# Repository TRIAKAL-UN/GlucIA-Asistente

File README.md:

# Proyecto GlucIA

## Home

### **Integrantes**
- Jeremy S. Arias Alegria
- David S. Ayala Salamanca
- Steven Cortes Gil
- Sara Duarte Acevedo
- David A. Orozco Gomez
- Oliver Emanuel Sucre Aular

---

### **Introducción**
GlucIA es un asistente de inteligencia artificial local implementado sobre una Raspberry Pi 5. Está diseñado para brindar acompañamiento confiable y accesible a personas con diabetes, ayudando a prevenir hipoglucemia e hiperglucemia mediante respuestas basadas en una base de datos médica y modelos de lenguaje ejecutados localmente, sin necesidad de internet.

---

### **Palabras clave**
Diabetes, Hipoglucemia, Hiperglucemia, Asistente con IA, Raspberry Pi 5, TinyLlama, Whisper, Piper TTS, RAG, Salud.

---

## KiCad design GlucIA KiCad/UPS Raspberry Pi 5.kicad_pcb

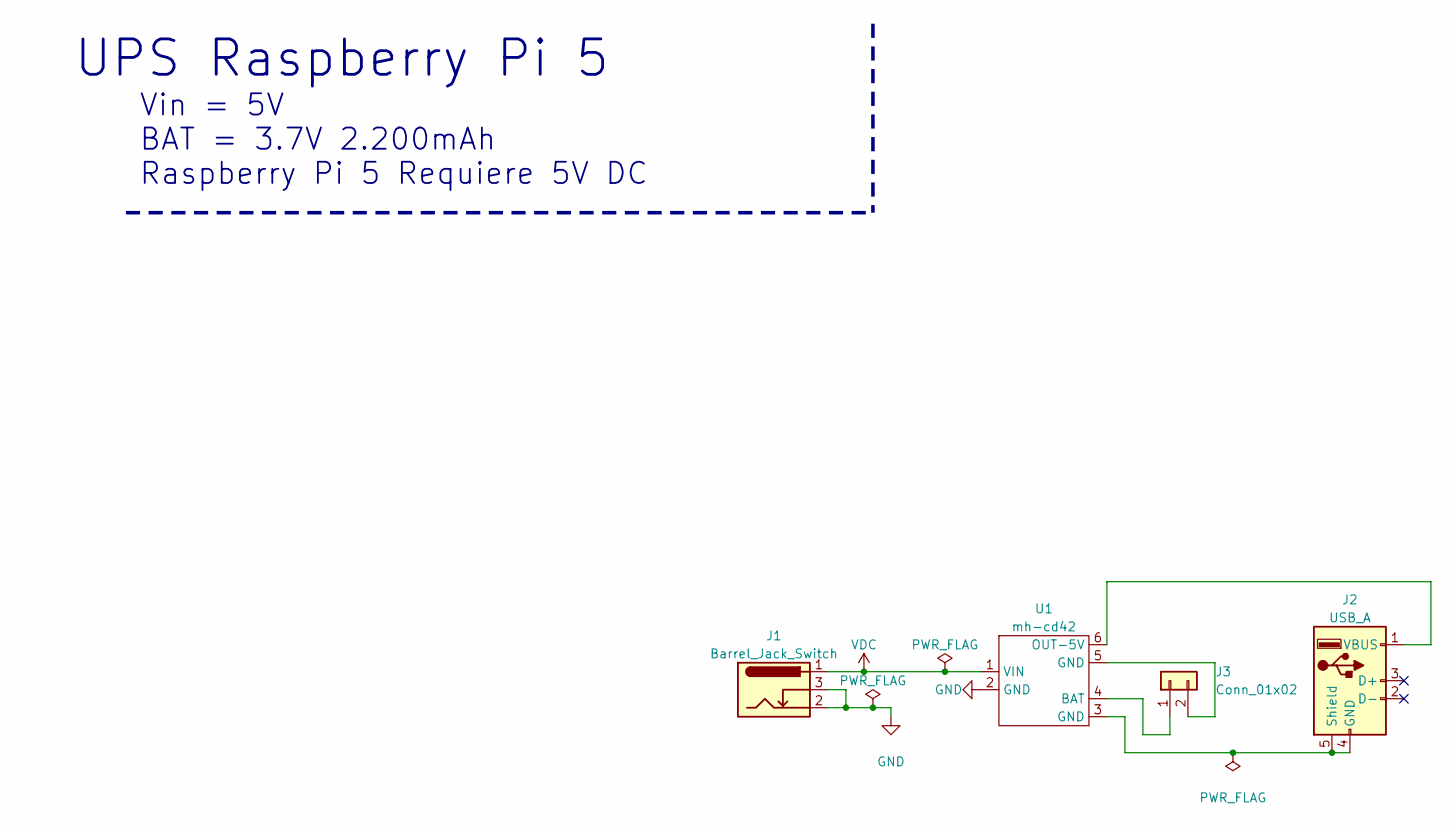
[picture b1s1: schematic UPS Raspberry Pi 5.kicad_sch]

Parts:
J1: Barrel_Jack_Switch; BarrelJack_Horizontal
J2: USB_A; USB_A_Molex_67643_Horizontal
J3: Conn_01x02; BatteryHolder_Keystone_2466_1xAAA
U1: mh-cd42; MH-CD42

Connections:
GND: J1.2, J1.3, U1.2 (GND)
unnamed: J2.4 (GND), J2.5 (Shield), U1.3 (GND)
unnamed: J2.1 (VBUS), U1.6 (OUT-5V)
unnamed: J3.1, U1.4 (BAT)
unnamed: J3.2, U1.5 (GND)
VDC: J1.1, U1.1 (VIN)

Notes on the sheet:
Vin = 5V BAT = 3.7V 2.200mAh Raspberry Pi 5 Requiere 5V DC
UPS Raspberry Pi 5

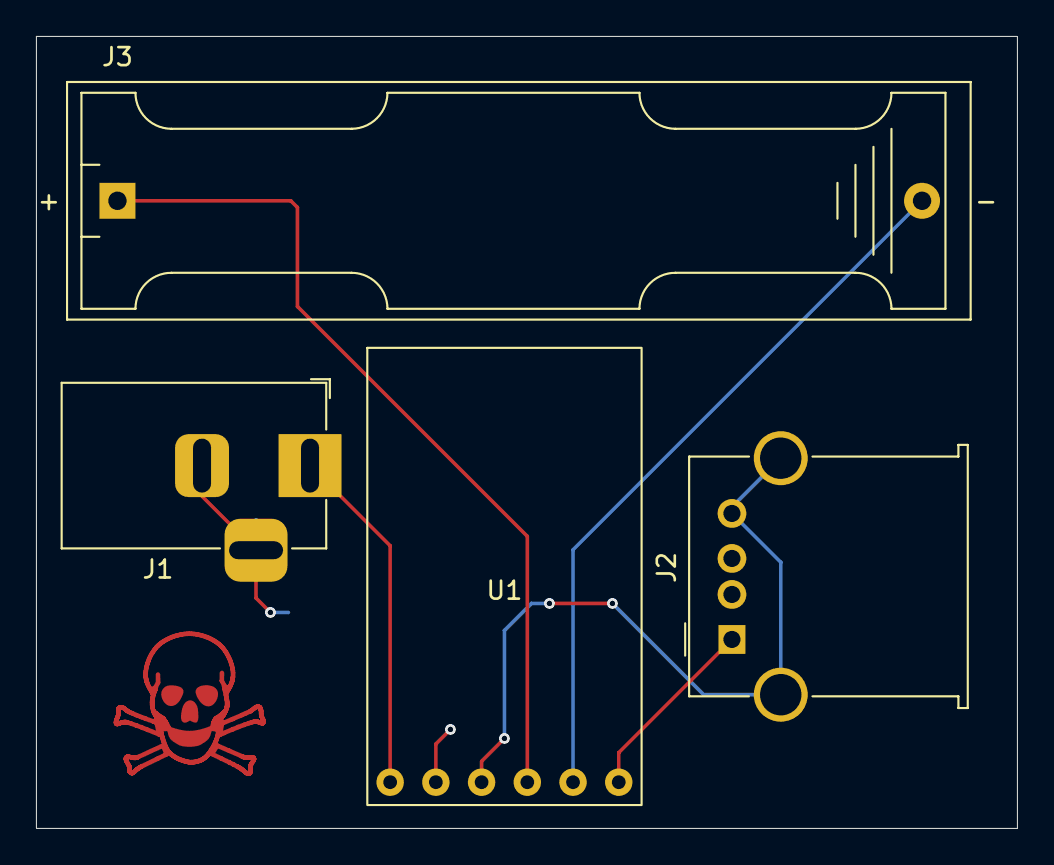
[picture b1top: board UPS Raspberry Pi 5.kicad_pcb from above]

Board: 2 copper layers, 54.5 x 44.0 mm, 4 parts (0 on the bottom side), 6 nets.

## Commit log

2025-07-09 README.md
2025-07-23 Create Codigo_GlucIA
    Codigo del Asistente con IA GlucIA
2025-07-23 Render 3D Carcasa
    Archivos Render, top, middle e inside
2025-07-23 Create Render
2025-07-23 Create Raspberry
2025-07-23 Create UPS
2025-07-23 Create Video GlucIA
2025-07-23 Create Video
2025-07-23 Create Anteproyecto
